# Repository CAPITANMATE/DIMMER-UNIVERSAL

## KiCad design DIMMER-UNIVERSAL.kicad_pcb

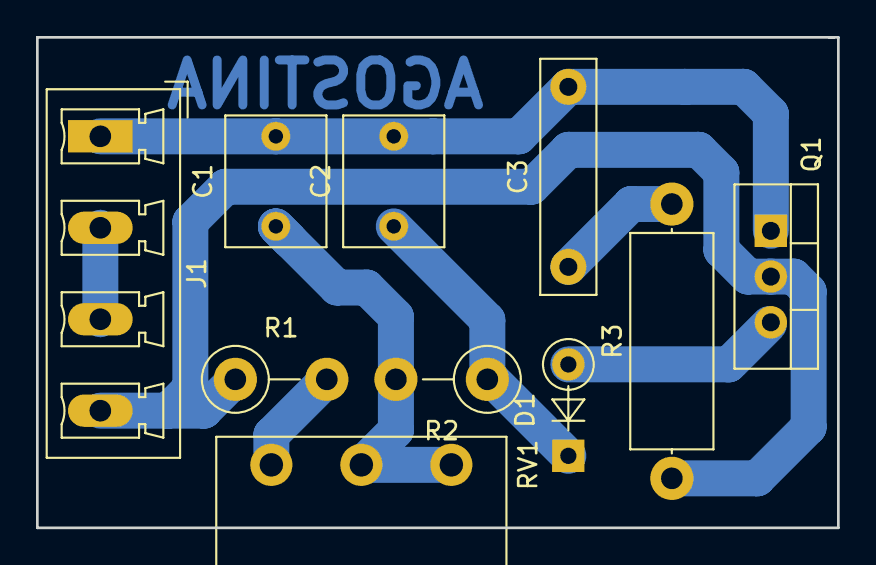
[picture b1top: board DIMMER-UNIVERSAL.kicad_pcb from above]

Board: 2 copper layers, 44.5 x 27.2 mm, 10 parts (0 on the bottom side), 8 nets.

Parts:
C1, C2: C; C_Rect_L7.2mm_W5.5mm_P5.00mm_FKS2_FKP2_MKS2_MKP2
C3: C; C_Rect_L13.0mm_W3.0mm_P10.00mm_FKS3_FKP3_MKS4
D1: DIAC; D_A-405_P5.08mm_Vertical_KathodeUp
J1: CONEXION; PhoenixContact_MCV-G_04x5.08mm_Vertical
Q1: BT136-800; TO-220-3_Vertical
R1, R2: R; R_Axial_DIN0411_L9.9mm_D3.6mm_P5.08mm_Vertical
R3: R; R_Axial_DIN0414_L11.9mm_D4.5mm_P15.24mm_Horizontal
RV1: R_POT; Potentiometer_Piher_PC-16_Single_Vertical

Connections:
unnamed: C1.1, R2.2, RV1.2, RV1.3
unnamed: C1.2, C2.2, C3.2, J1.1, Q1.1
unnamed: C2.1, D1.1, R2.1
unnamed: C3.1, R3.2
unnamed: D1.2, Q1.3
unnamed: J1.2, J1.3
unnamed: J1.4, Q1.2, R1.1, R3.1
unnamed: R1.2, RV1.1

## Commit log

2019-02-09 new file: DIMMER-UNIVERSAL.kicad_pcb new file: DIMMER-UNIVERSAL.lib new file: DIMMER-UNIVERSAL.pro new file: DIMMER-UNIVERSAL.sch
2019-02-09 DIMMER-UNIVERSAL.bak DIMMER-UNIVERSAL.kicad_pcb-bak DIMMER-UNIVERSAL.net
2019-02-09 new file: DIMMER-UNIVERSAL.bak new file: DIMMER-UNIVERSAL.kicad_pcb-bak new file: DIMMER-UNIVERSAL.net
2019-02-09 new file: DIMMER-UNIVERSAL-cache.lib new file: DIMMER-UNIVERSAL.bak new file: DIMMER-UNIVERSAL.kicad_pcb-bak new file: DIMMER-UNIVERSAL.net
